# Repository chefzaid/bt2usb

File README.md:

# bt2usb

bt2usb is Rust firmware for an nRF52840 that lets a Bluetooth LE keyboard and
mouse work through a monitor's USB hub. It connects to BLE HID peripherals and
presents a standard USB keyboard, mouse, and consumer-control device to the PC,
with an SSD1306 OLED and three buttons for pairing and status.

## Status

This is development firmware. Its behavior is implemented and covered by host
tests, embedded builds, and a Renode simulation, but it has not yet passed the
[first-flash hardware checklist](docs/first-flash.md) on a real board. What
works today is in [Features](docs/features.md); every task, done and open, is in
[TODO.md](TODO.md); known security limits are in [Security](docs/security.md).

## Documentation

- [Features and how to use it](docs/features.md)
- [Hardware, wiring, configuration and custom board](docs/hardware.md)
- [First flash: board bring-up checklist](docs/first-flash.md)
- [Architecture overview and ADR index](docs/architecture.md)
- [Data model reference](docs/data-model.md)
- [Development guide](docs/development.md)
- [Testing guide](docs/testing.md) and [validation records](docs/validation-records.md)
- [Code quality](docs/code-quality.md)
- [Deployment: releases, provenance and flashing](docs/deployment.md)
- [Operations runbook](docs/operations.md)
- [Security reference](docs/security.md) and [security policy](SECURITY.md)
- [Task reference](maskfile.md)

## Roadmap

[TODO.md](TODO.md) is the complete work plan: finished work is checked off with
its source references, and open work carries a priority and an acceptance
criterion. The [status at a glance](TODO.md#status-at-a-glance) table shows what
is done and what is left in each area. Hardware gates stay open until board
evidence exists.

## Quick Start

You need an nRF52840-DK, an SSD1306 128×64 I2C display, and Rust through
rustup; see [hardware](docs/hardware.md) for wiring.

```sh
rustup target add thumbv7em-none-eabihf
cargo install --locked probe-rs-tools mask
mask test                # host tests, no board needed
mask build --release     # bridge and self-test firmware
```

On a new board, follow [first flash](docs/first-flash.md) to install SoftDevice
S140, run the self-test, and validate the bridge; then `mask run --release`.
[Getting started](docs/development.md#getting-started) walks through the
no-hardware, simulation, and board paths, including Windows/WSL and the
devcontainer.

## License

GNU GPL v3; see [LICENSE](LICENSE). Nordic SoftDevice S140 is obtained
separately from Nordic; see
[third-party components](docs/deployment.md#third-party-components-and-licenses).

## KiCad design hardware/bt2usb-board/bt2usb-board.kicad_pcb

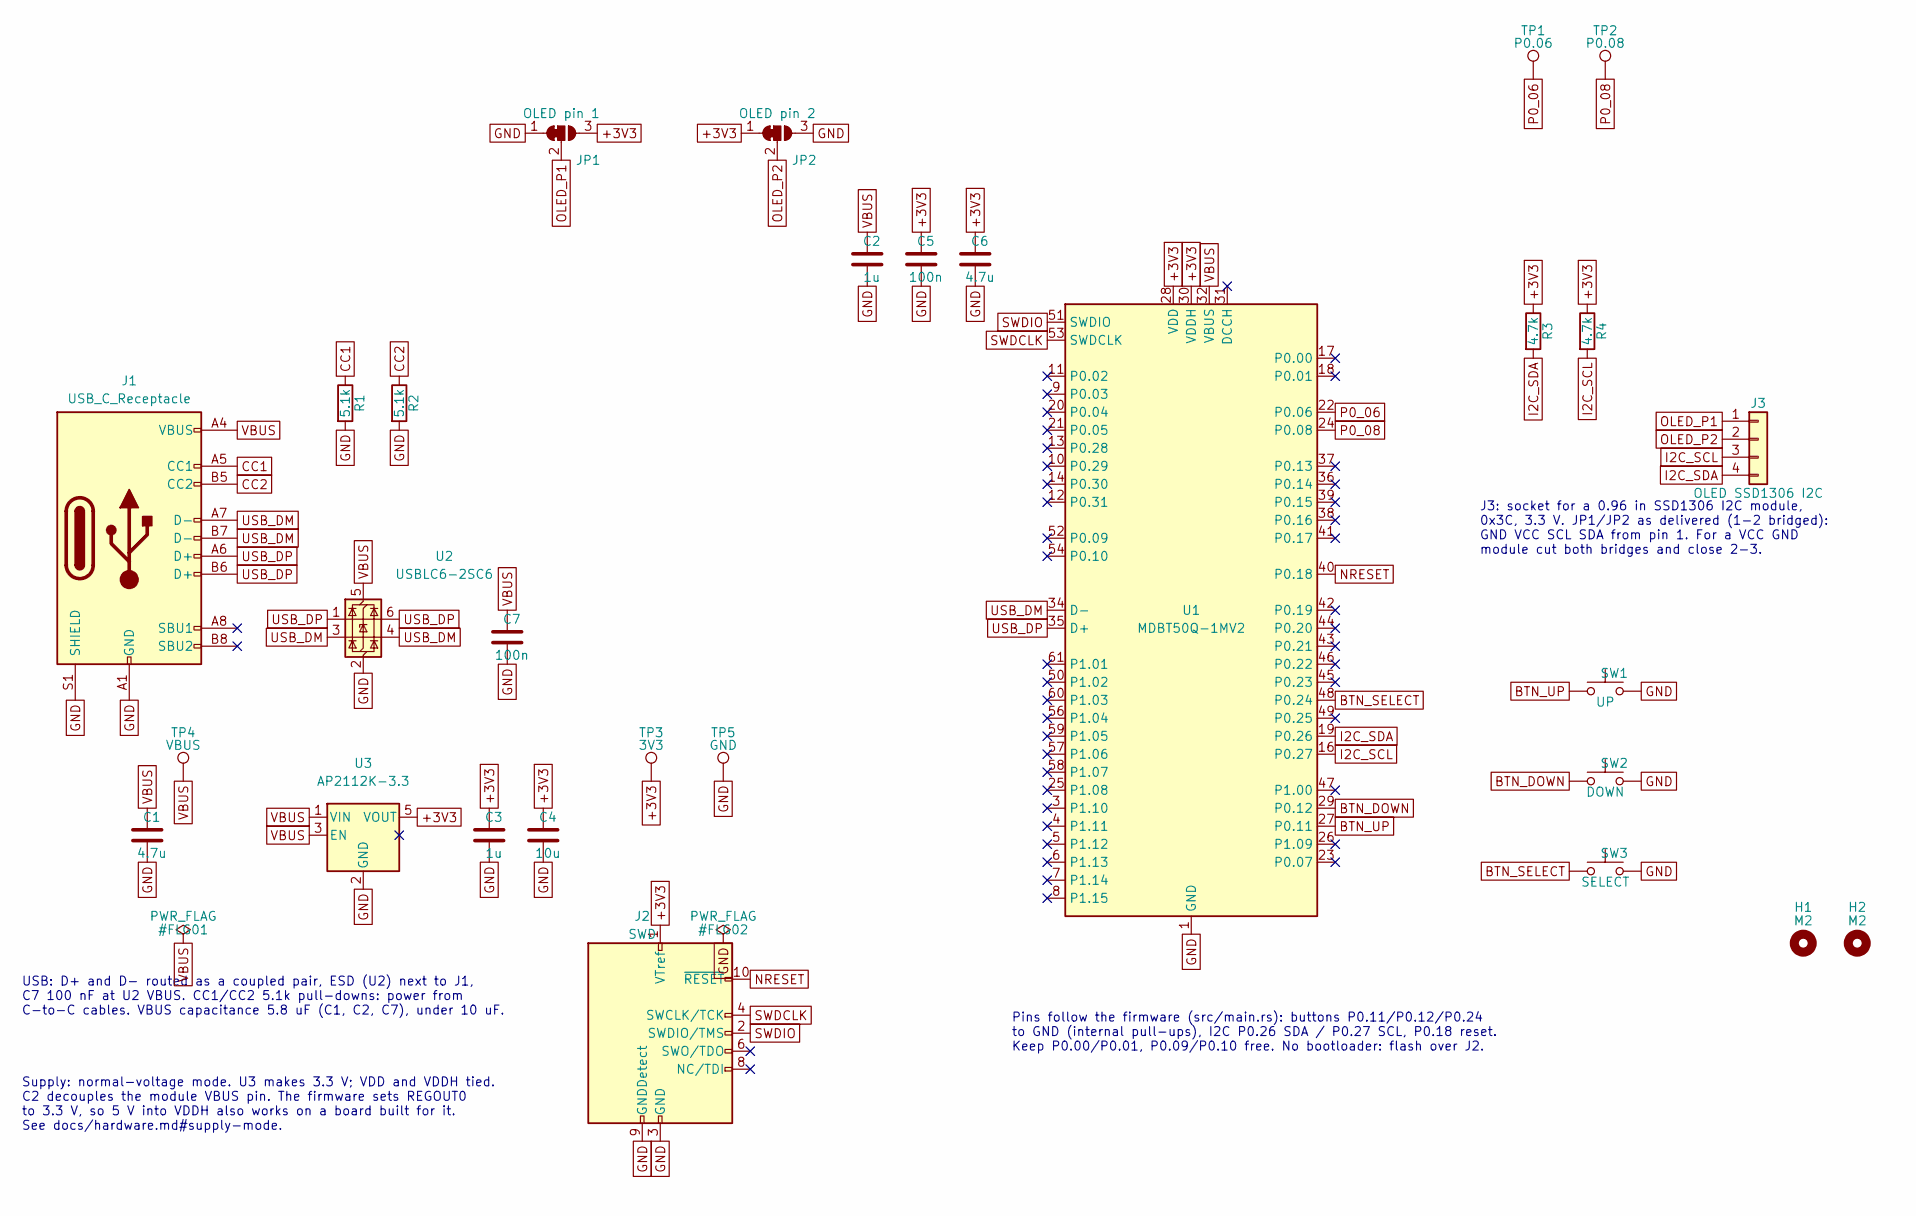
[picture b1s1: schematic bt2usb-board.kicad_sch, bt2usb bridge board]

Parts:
C1, C6: 4.7u; C_0603_1608Metric
C2, C3: 1u; C_0603_1608Metric
C4: 10u; C_0603_1608Metric
C5, C7: 100n; C_0603_1608Metric
H1, H2: M2; MountingHole_2.2mm_M2
J1: USB_C_Receptacle; USB_C_Receptacle_GCT_USB4105-xx-A_16P_TopMnt_Horizontal; MPN USB4105-GF-A
J2: SWD; PinHeader_2x05_P1.27mm_Vertical_SMD; MPN FTSH-105-01-L-DV-K
J3: OLED SSD1306 I2C; PinSocket_1x04_P2.54mm_Vertical
JP1: OLED pin 1; SolderJumper-3_P1.3mm_Bridged12_RoundedPad1.0x1.5mm
JP2: OLED pin 2; SolderJumper-3_P1.3mm_Bridged12_RoundedPad1.0x1.5mm
R1, R2: 5.1k; R_0603_1608Metric
R3, R4: 4.7k; R_0603_1608Metric
SW1: UP; SW_SPST_PTS645Sx43SMTR92; MPN PTS645SM43SMTR92 LFS
SW2: DOWN; SW_SPST_PTS645Sx43SMTR92; MPN PTS645SM43SMTR92 LFS
SW3: SELECT; SW_SPST_PTS645Sx43SMTR92; MPN PTS645SM43SMTR92 LFS
TP1: P0.06; TestPoint_Pad_D1.0mm
TP2: P0.08; TestPoint_Pad_D1.0mm
TP3: 3V3; TestPoint_Pad_D1.0mm
TP4: VBUS; TestPoint_Pad_D1.0mm
TP5: GND; TestPoint_Pad_D1.0mm
U1: MDBT50Q-1MV2; Raytac_MDBT50Q; MPN MDBT50Q-1MV2
U2: USBLC6-2SC6; SOT-23-6; MPN USBLC6-2SC6
U3: AP2112K-3.3; SOT-23-5; MPN AP2112K-3.3TRG1

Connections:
+3V3: C3.1, C4.1, C5.1, C6.1, J2.1 (VTref), JP1.3 (B), JP2.1 (A), R3.1, R4.1, TP3.1, U1.28 (VDD), U1.30 (VDDH), U3.5 (VOUT)
BTN_DOWN: SW2.1, U1.29 (P0.12)
BTN_SELECT: SW3.1, U1.48 (P0.24)
BTN_UP: SW1.1, U1.27 (P0.11)
CC1: J1.A5 (CC1), R1.1
CC2: J1.B5 (CC2), R2.1
GND: C1.2, C2.2, C3.2, C4.2, C5.2, C6.2, C7.2, J1.A1 (GND), J1.A12 (GND), J1.B1 (GND), J1.B12 (GND), J1.S1 (SHIELD), J2.3 (GND), J2.5 (GND), J2.9 (GNDDetect), JP1.1 (A), JP2.3 (B), R1.2, R2.2, SW1.2, SW2.2, SW3.2, TP5.1, U1.1 (GND), U1.2 (GND), U1.15 (GND), U1.33 (GND), U1.55 (GND), U2.2 (GND), U3.2 (GND)
I2C_SCL: J3.3, R4.2, U1.16 (P0.27)
I2C_SDA: J3.4, R3.2, U1.19 (P0.26)
NRESET: J2.10 (~RESET), U1.40 (P0.18)
OLED_P1: J3.1, JP1.2 (C)
OLED_P2: J3.2, JP2.2 (C)
P0_06: TP1.1, U1.22 (P0.06)
P0_08: TP2.1, U1.24 (P0.08)
SWDCLK: J2.4 (SWCLK/TCK), U1.53 (SWDCLK)
SWDIO: J2.2 (SWDIO/TMS), U1.51 (SWDIO)
USB_DM: J1.A7 (D-), J1.B7 (D-), U1.34 (D-), U2.3 (I/O2), U2.4 (I/O2)
USB_DP: J1.A6 (D+), J1.B6 (D+), U1.35 (D+), U2.1 (I/O1), U2.6 (I/O1)
VBUS: C1.1, C2.1, C7.1, J1.A4 (VBUS), J1.A9 (VBUS), J1.B4 (VBUS), J1.B9 (VBUS), TP4.1, U1.32 (VBUS), U2.5 (VBUS), U3.1 (VIN), U3.3 (EN)

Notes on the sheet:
USB: D+ and D- routed as a coupled pair, ESD (U2) next to J1, C7 100 nF at U2 VBUS. CC1/CC2 5.1k pull-downs: power from C-to-C cables. VBUS capacitance 5.8 uF (C1, C2, C7), under 10 uF.
Supply: normal-voltage mode. U3 makes 3.3 V; VDD and VDDH tied. C2 decouples the module VBUS pin. The firmware sets REGOUT0 to 3.3 V, so 5 V into VDDH also works on a board built for it. See docs/hardware.md#supply-mode.
Pins follow the firmware (src/main.rs): buttons P0.11/P0.12/P0.24 to GND (internal pull-ups), I2C P0.26 SDA / P0.27 SCL, P0.18 reset. Keep P0.00/P0.01, P0.09/P0.10 free. No bootloader: flash over J2.
J3: socket for a 0.96 in SSD1306 I2C module, 0x3C, 3.3 V. JP1/JP2 as delivered (1-2 bridged): GND VCC SCL SDA from pin 1. For a VCC GND module cut both bridges and close 2-3.

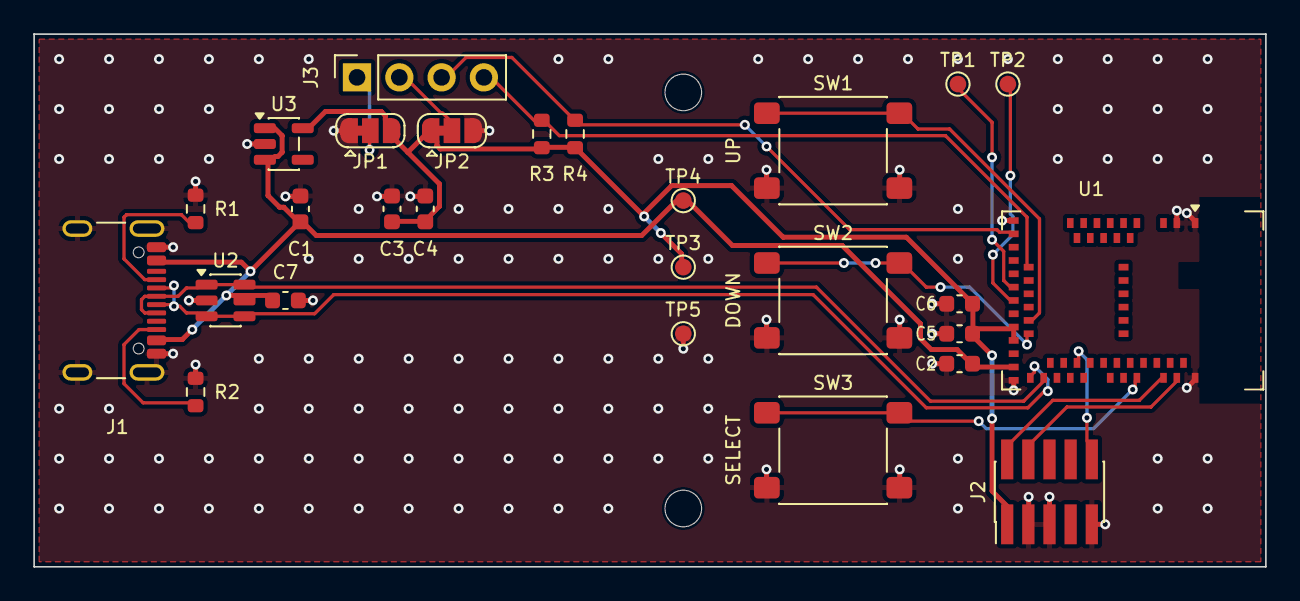
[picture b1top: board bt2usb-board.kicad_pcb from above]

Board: 2 copper layers, 74.0 x 32.0 mm, 29 parts (0 on the bottom side), 19 nets.

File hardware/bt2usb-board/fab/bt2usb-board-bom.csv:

Item,Qty,References,Value,Footprint,Manufacturer,MPN,Notes
1,2,C1 C6,4.7u,C_0603_1608Metric,Any,Any,"Ceramic X5R or X7R, 10 V or more"
2,2,C2 C3,1u,C_0603_1608Metric,Any,Any,"Ceramic X5R or X7R, 10 V or more"
3,1,C4,10u,C_0603_1608Metric,Any,Any,"Ceramic X5R or X7R, 10 V or more"
4,2,C5 C7,100n,C_0603_1608Metric,Any,Any,"Ceramic X5R or X7R, 10 V or more"
5,1,J1,USB_C_Receptacle,USB_C_Receptacle_GCT_USB4105-xx-A_16P_TopMnt_Horizontal,GCT,USB4105-GF-A,
6,1,J2,SWD,PinHeader_2x05_P1.27mm_Vertical_SMD,Samtec,FTSH-105-01-L-DV-K,ARM 10-pin 1.27 mm SWD header
7,1,J3,OLED SSD1306 I2C,PinSocket_1x04_P2.54mm_Vertical,Any,Any,"1x4 2.54 mm female socket, 8.5 mm tall; the 0.96"" SSD1306 I2C module (address 0x3C) plugs in. JP1/JP2 on the board set its supply pin order"
8,2,R1 R2,5.1k,R_0603_1608Metric,Any,Any,Thick film 1%
9,2,R3 R4,4.7k,R_0603_1608Metric,Any,Any,Thick film 1%
10,1,SW1,UP,SW_SPST_PTS645Sx43SMTR92,C&K,PTS645SM43SMTR92 LFS,"6 x 6 mm tactile switch, 4.3 mm tall, 50,000 cycles or more"
11,1,SW2,DOWN,SW_SPST_PTS645Sx43SMTR92,C&K,PTS645SM43SMTR92 LFS,"6 x 6 mm tactile switch, 4.3 mm tall, 50,000 cycles or more"
12,1,SW3,SELECT,SW_SPST_PTS645Sx43SMTR92,C&K,PTS645SM43SMTR92 LFS,"6 x 6 mm tactile switch, 4.3 mm tall, 50,000 cycles or more"
13,1,U1,MDBT50Q-1MV2,Raytac_MDBT50Q,Raytac,MDBT50Q-1MV2,"Pre-certified nRF52840 module, chip antenna"
14,1,U2,USBLC6-2SC6,SOT-23-6,STMicroelectronics,USBLC6-2SC6,
15,1,U3,AP2112K-3.3,SOT-23-5,Diodes Incorporated,AP2112K-3.3TRG1,

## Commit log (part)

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2024-12-07 Basic converter
2025-02-17 Fixing pairing issues
2025-05-28 Terminal implementation and some fixes
2026-02-21 Full implementation
2026-02-21 Updated REAMDE
2026-03-11 Fix build
2026-06-21 feat: Enhance Bluetooth-to-USB HID bridge functionality and storage
2026-06-21 Bug fixes
2026-06-22 Refactor BLE module to integrate coordinator logic and enhance UI state management
2026-06-22 Add unit tests for connection manager and refine HID report parsing
2026-06-22 Refactor: split oversized modules, unify HID logic, add Renode sim + tests
    - Split files >500 LOC: lib.rs/coordinator.rs tests into sibling files,
    storage byte-codec into storage/codec.rs
    - Unify HID classification on the real hid module (drop lib.rs duplicate +
    dead hid/tests.rs); host tests now cover report_protocol + hint classifier
    - SoftDevice-free Renode sim build + robot test; install-renode.sh
    - Firmware fixes (USB VBUS, interrupt priorities, BLE disconnect, scan timeout,
2026-06-22 Ignore Renode/Robot test-result artifacts
2026-06-22 Updated README details
2026-06-22 Update async tasks documentation for clarity and completeness
2026-06-22 Update README to clarify functionality in simple terms
2026-06-23 Upgrade crates versions and fix latent issues
2026-06-23 Implement keyboard LED state handling for BLE keyboard passthrough
2026-06-23 Enhance power management and activity tracking for HID devices
2026-06-23 Add versioned framing for paired-device flash records and update serialization logic
2026-06-23 Enhance mouse report handling to support 5-byte reports with horizontal scroll and update related tests
2026-06-24 Refactor display handling to use async I2C for non-blocking operations and update related functions
2026-06-24 Clarify Renode GPIO→GPIOTE injection issue
2026-06-30 Remove VSCode settings

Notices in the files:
README.md:
License: GPL 3.0
